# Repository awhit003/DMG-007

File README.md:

# DMG-007

**DMG-007** is a modern hardware integration and re-engineering project for the original Nintendo Game Boy (DMG) form factor. 

The core philosophy of DMG-007 is **zero donor DMG-001 parts**: the console is built entirely from newly fabricated PCBs, modern off-the-shelf components, and automated surface-mount assembly. The **sole donor component** in the entire build is a salvaged **SGB-CPU** from a Japanese Super Famicom / Super Game Boy cartridge.

The designs and documentation are fabrication-agnostic and universally compatible with major PCB fabrication services including **OSH Park**, **PCBWay**, and **JLCPCB**.

---

## 🎯 Design Parameters & Architecture

1. **Zero DMG-001 Consoles Sacrificed:**
   - No original DMG-001 motherboards, power boards, audio boards, or screens are consumed.
   - The primary processor is an **SGB-CPU** (harvested from readily available Japanese Super Game Boy cartridges).
   - VRAM, work RAM, crystal oscillators, and audio amplification all use modern, commercially available replacement silicon and passives.

2. **Automated Surface-Mount (SMT) Assembly:**
   - Boards are designed with standard surface-mount packages (0805/0603 passives, standard IC packages) to allow automated pick-and-place assembly.
   - SGB-CPU (U1) and through-hole mechanical connectors (cartridge slot, headphone jack, battery contacts) are populated post-assembly.
   - Vendor-specific manufacturing instructions (e.g., JLCPCB/JLCONE tooling and LCSC part mappings) are maintained in dedicated vendor documentation.

3. **High-Performance Reflective Display (Sharp RLCD):**
   - Incorporates a modern ultra-fast 1-bit Reflective LCD panel (Sharp Memory LCD / RLCD `LS032B7DD02`, 3.2", 336×536).
   - Preserves the authentic, glare-free, outdoor-readable aesthetic of the original monochrome DMG without backlights or motion smear.
   - Driven by an on-board Raspberry Pi RP2040 utilizing clean-room PIO capture and 2×2 Bayer dithering.

4. **"God View" VRAM Bus Snooping (256×256 Viewport Expansion):**
   - The Sharp driver board includes a dedicated **24-pin 0.5mm FPC expansion port (`J4_VRAM_SNOOP`)**.
   - Snoops the Game Boy VRAM bus (`A0–A12`, `D0–D7`, `/WR`) via an optional parasitic flex cable.
   - Enables hardware capture of the entire internal 256×256 pixel background tilemap in real time, unlocking full-canvas wide-angle rendering beyond the clipped 160×144 PPU viewport.

5. **Clean Power Delivery:**
   - Dedicated high-efficiency synchronous buck-boost regulation (`DMGC-PWR-01`) delivering a rock-solid, isolated 5V rail capable of supporting the RLCD controller and modern audio amplifier across varying battery discharge curves.

---

## 🧩 Integrated Hardware Components & Attribution

This project brings together foundational designs created by talented open-source hardware developers across the retro-modding community:

| Module | Source Design | Original Author | Upstream License | Function in DMG-007 |
| :--- | :--- | :--- | :--- | :--- |
| **Motherboard** | [Super-DMG-01](https://github.com/kamicane/Super-DMG-01) | **kamicane** (Valerio Proietti) | CC BY-SA 4.0 | Main system logic board engineered to host the SGB-CPU, modern RAM, and USB-C power integration. |
| **Audio Board** | [Super DMG JACK](https://github.com/kamicane/Super-DMG-01) | **kamicane** (Valerio Proietti) | CC BY-SA 4.0 | Independent headphone and speaker audio board utilizing a PAM8302 mono Class-D amplifier. |
| **Power Supply** | [DMGC-PWR-01](https://github.com/MouseBiteLabs/Game-Boy-DMG-Color) | **MouseBiteLabs** (Bucket Mouse) | CC BY-SA 4.0 | High-efficiency buck-boost regulator board (TPS630702 based) with undervoltage latching. |
| **Display Subsystem**| Clean-Room Sharp RLCD Driver | DMG-007 Project | CC BY-SA 4.0 | RP2040 controller driving Sharp LS032B7DD02 with PIO capture, 2×2 Bayer dither, and 24-pin VRAM snooping bus. |

For detailed license terms and derivative compliance requirements, see [NOTICE.md](NOTICE.md) and [LICENSE](LICENSE).

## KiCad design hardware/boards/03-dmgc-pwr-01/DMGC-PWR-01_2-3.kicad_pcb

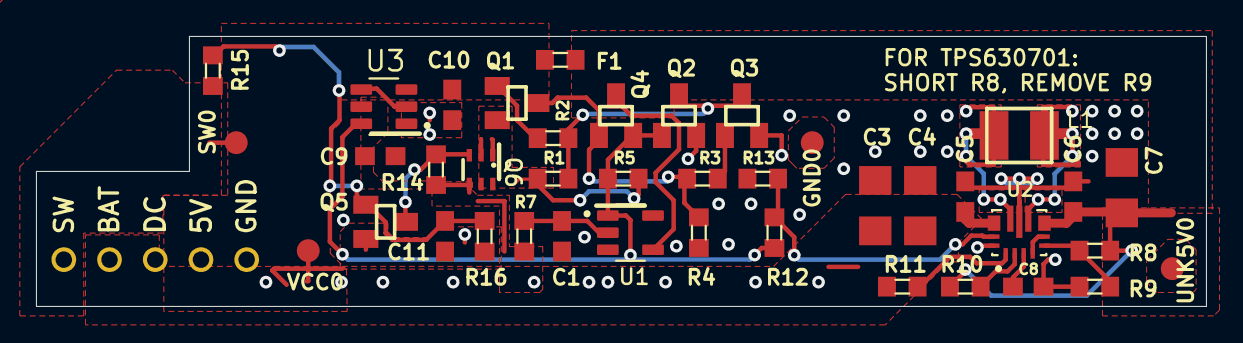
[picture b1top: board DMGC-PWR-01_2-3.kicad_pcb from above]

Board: 2 copper layers, 65.0 x 15.0 mm, 41 parts (0 on the bottom side), 22 nets.

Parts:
C1, C5, C6: 10uF; C0603
C3, C4: 22uF; C1206
C7: 47uF; C1206
C8, C9, C11: 100nF; C0603
C10: 10nF; C0603
F1: 1A; R0603
GND0: PTR1B1,27; B1,27
JP1: JP5
L1: 1.5uH; 1212
Q1: MMBT3906LT1SMD; SOT23-BEC
Q2, Q4, Q5: 2N7002; SOT23
Q3: 3904; SOT23-BEC
Q6: SI1401EDH; SOT363_INFINEON
R1, R4, R7, R9, R10, R11, R16: 100k; R0603
R2, R3, R5, R13, R14: 10k; R0603
R8: 523k; R0603
R12: 20k; R0603
R15: 1k; R0603
SW0: PTR1B1,27; B1,27
U1: TPS3840; SOT-23-5
U2: TPS63070RNMR; VREG_TPS63070RNMR
U3: TPS3702; SOT-23-6
UNK5V0: PTR1B1,27; B1,27
VCC0: PTR1B1,27; B1,27

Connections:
+5V: C10.1, F1.1, JP1.2, U3.3
/MR: Q4.3, U1.4
EN: R12.2, R13.1, U2.14
GND: C1.2, C3.2, C4.2, C5.2, C6.2, C7.2, C8.2, C9.2, C10.2, C11.2, GND0.TP, JP1.1, Q2.2, Q3.E, Q5.2, R4.1, R9.1, R13.2, R16.1, U1.3, U2.4, U2.6, U2.10, U2.15, U3.2, U3.4
unnamed: C1.1, R7.1, U1.2
unnamed: L1.2, U2.11
unnamed: L1.1, U2.9
unnamed: R10.2, U2.2
unnamed: C8.1, U2.3
unnamed: R8.1, R9.2, U2.5
unnamed: Q5.3, Q6.3, R14.2
unnamed: C11.1, Q5.1, R15.2, R16.2
unnamed: Q1.B, R2.1
unnamed: Q1.C, Q4.1, R3.1, R4.2
unnamed: Q3.B, R3.2
unnamed: Q2.3, Q3.C, R1.1, R2.2
PS: R11.1, U2.1
PSU_EN: Q2.1, Q4.2, R5.2, R12.1, U1.1, U3.6
SW: JP1.5, R15.1, SW0.TP
VCC: C3.1, C4.1, C5.1, C9.1, JP1.3, JP1.4, Q6.4, R7.2, R11.2, R14.1, U2.12_13, U3.5, VCC0.TP
VCC_LATCH: Q1.E, Q6.1, Q6.2, Q6.5, Q6.6, R1.2, R5.1
VOUT: C6.1, C7.1, F1.2, R8.2, R10.1, U2.7_8, UNK5V0.TP
